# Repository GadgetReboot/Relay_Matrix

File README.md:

# Relay_Matrix
Relay matrix for routing signal inputs to various outputs

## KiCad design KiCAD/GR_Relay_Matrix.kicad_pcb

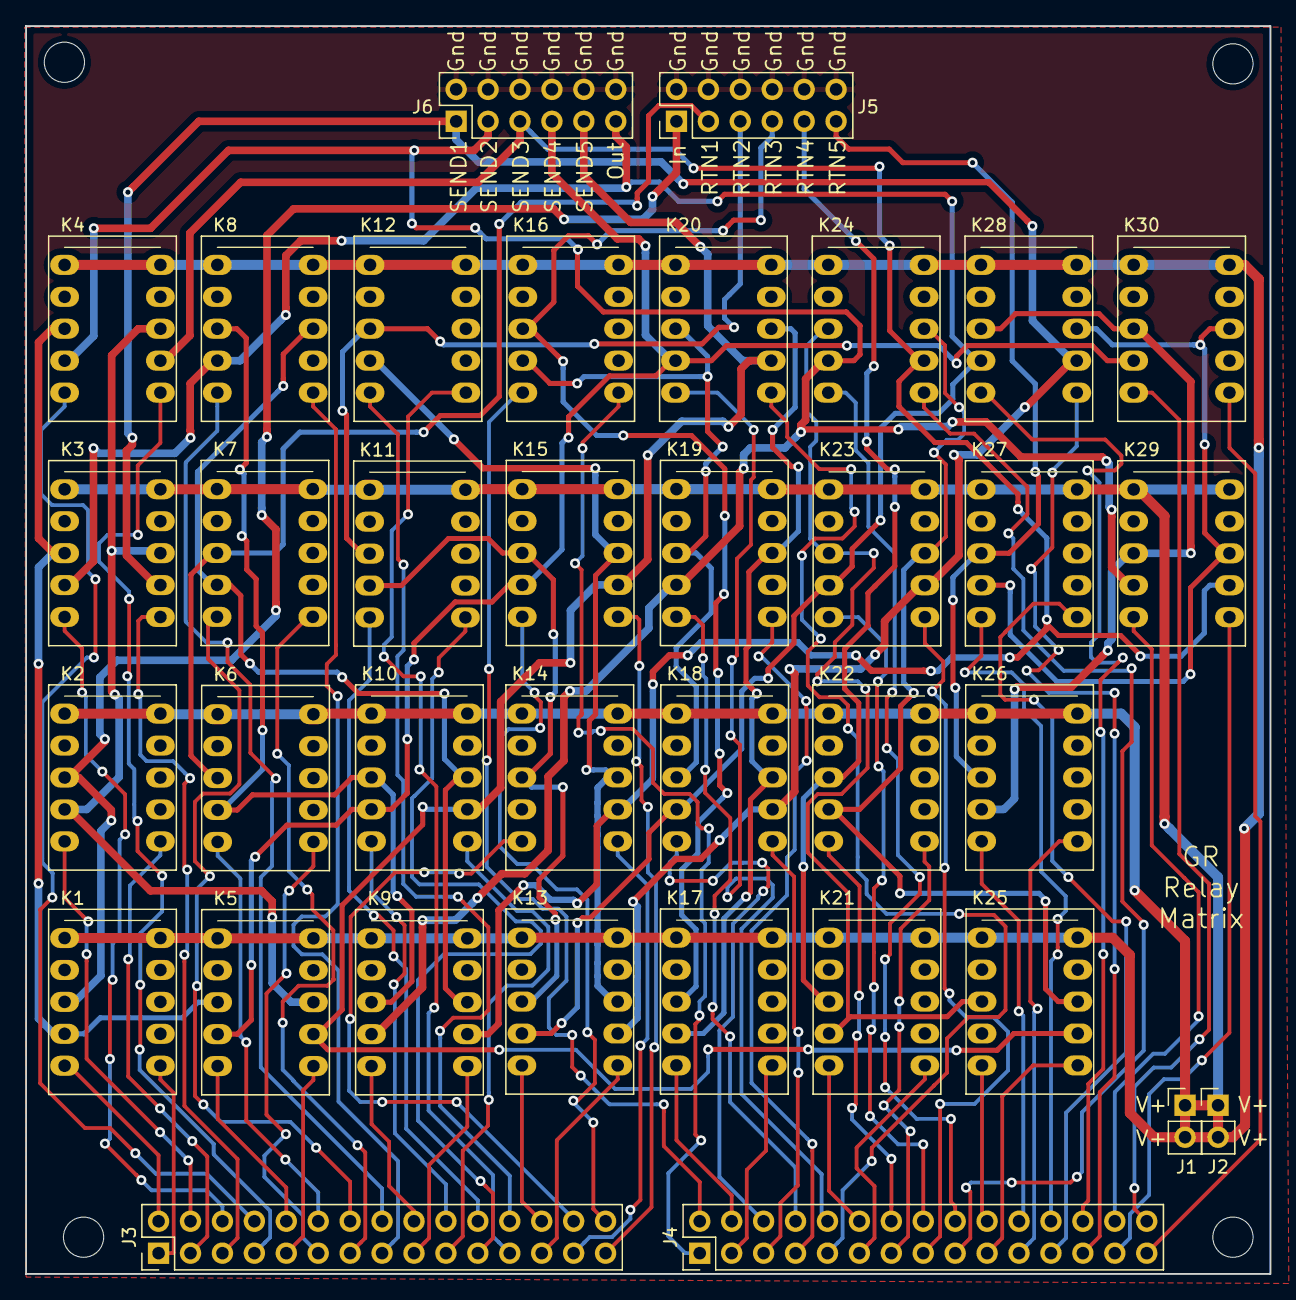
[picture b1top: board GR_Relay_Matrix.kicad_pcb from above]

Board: 2 copper layers, 99.0 x 99.3 mm, 40 parts (0 on the bottom side), 86 nets.

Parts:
J1, J2: Conn_01x02; PinHeader_1x02_P2.54mm_Vertical
J3, J4: Conn_02x15_Odd_Even; PinHeader_2x15_P2.54mm_Vertical
J5, J6: Conn_02x06_Odd_Even; PinHeader_2x06_P2.54mm_Vertical
K1, K2, K3, K4, K5, K6, K7, K8, K9, K10, K11, K12, K13, K14, K15, K16, K17, K18, K19, K20, K21, K22, K23, K24, K25, K26, K27, K28, K29, K30: EA2-5TNJ; Relay_DPDT_FRT5
MH1, MH2, MH3, MH4: MountingHole; MountingHole_3.2mm_M3

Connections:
/Main_In: J5.1, K1.3, K2.3
/Main_Out: J6.11, K3.4, K8.4, K13.4, K18.4, K23.4, K28.4
/X1_Reset_A: J3.1, K1.6
/X1_Reset_B: J3.3, K2.6
/X1_Set_A: J3.2, K1.5
/X1_Set_B: J3.4, K2.5
/X2_Path: J5.3, K6.3, K7.3
/X2_Reset_A: J3.11, K6.6
/X2_Reset_B: J3.13, K7.6
/X2_Set_A: J3.12, K6.5
/X2_Set_B: J3.14, K7.5
/X3_Path: J5.5, K11.3, K12.3
/X3_Reset_A: J3.21, K11.6
/X3_Reset_B: J3.23, K12.6
/X3_Set_A: J3.22, K11.5
/X3_Set_B: J3.24, K12.5
/X4_Path: J5.7, K16.3, K17.3
/X4_Reset_A: J4.1, K16.6
/X4_Reset_B: J4.3, K17.6
/X4_Set_A: J4.2, K16.5
/X4_Set_B: J4.4, K17.5
/X5_Path: J5.9, K21.3, K22.3
/X5_Reset_A: J4.11, K21.6
/X5_Reset_B: J4.13, K22.6
/X5_Set_A: J4.12, K21.5
/X5_Set_B: J4.14, K22.5
/X6_Path: J5.11, K26.3, K27.3
/X6_Reset_A: J4.21, K26.6
/X6_Reset_B: J4.23, K27.6
/X6_Set_A: J4.22, K26.5
/X6_Set_B: J4.24, K27.5
/Y1_2_Reset: J3.5, K3.6
/Y1_2_Set: J3.6, K3.5
/Y2_Path: J6.1, K3.7, K13.7, K18.7, K23.7, K28.7
/Y3_4_Reset: J3.7, K4.6
/Y3_4_Set: J3.8, K4.5
/Y3_Path: J6.3, K4.4, K9.4, K19.4, K24.4, K29.4
/Y4_Path: J6.5, K4.7, K9.7, K14.7, K24.7, K29.7
/Y5_6_Reset: J3.9, K5.6
/Y5_6_Set: J3.10, K5.5
/Y5_Path: J6.7, K5.4, K10.4, K15.4, K20.4, K30.4
/Y6_Path: J6.9, K5.7, K10.7, K15.7, K20.7, K25.7
/Y7_8_Reset: J3.15, K8.6
/Y7_8_Set: J3.16, K8.5
/Y9_10_Reset: J3.17, K9.6
/Y9_10_Set: J3.18, K9.5
/Y11_12_Reset: J3.19, K10.6
/Y11_12_Set: J3.20, K10.5
/Y13_14_Reset: J3.25, K13.6
/Y13_14_Set: J3.26, K13.5
/Y15_16_Reset: J3.27, K14.6
/Y15_16_Set: J3.28, K14.5
/Y17_18_Reset: J3.29, K15.6
/Y17_18_Set: J3.30, K15.5
/Y19_20_Reset: J4.5, K18.6
/Y19_20_Set: J4.6, K18.5
/Y21_22_Reset: J4.7, K19.6
/Y21_22_Set: J4.8, K19.5
/Y23_24_Reset: J4.9, K20.6
/Y23_24_Set: J4.10, K20.5
/Y25_26_Reset: J4.15, K23.6
/Y25_26_Set: J4.16, K23.5
/Y27_28_Reset: J4.17, K24.6
/Y27_28_Set: J4.18, K24.5
/Y29_30_Reset: J4.19, K25.6
/Y29_30_Set: J4.20, K25.5
/Y31_32_Reset: J4.25, K28.6
/Y31_32_Set: J4.26, K28.5
/Y33_34_Reset: J4.27, K29.6
/Y33_34_Set: J4.28, K29.5
/Y35_36_Reset: J4.29, K30.6
/Y35_36_Set: J4.30, K30.5
GNDREF: J5.2, J5.4, J5.6, J5.8, J5.10, J5.12, J6.2, J6.4, J6.6, J6.8, J6.10, J6.12
unnamed: K1.4, K3.3, K4.3, K5.3
unnamed: K2.4, K3.8, K4.8, K5.8
unnamed: K6.4, K8.3, K9.3, K10.3
unnamed: K7.4, K8.8, K9.8, K10.8
unnamed: K11.4, K13.3, K14.3, K15.3
unnamed: K12.4, K13.8, K14.8, K15.8
unnamed: K16.4, K18.3, K19.3, K20.3
unnamed: K17.4, K18.8, K19.8, K20.8
unnamed: K21.4, K23.3, K24.3, K25.3
unnamed: K22.4, K23.8, K24.8, K25.8
unnamed: K26.4, K28.3, K29.3, K30.3
unnamed: K27.4, K28.8, K29.8, K30.8
Vdrive: J1.1, J1.2, J2.1, J2.2, K1.1, K1.10, K2.1, K2.10, K3.1, K3.10, K4.1, K4.10, K5.1, K5.10, K6.1, K6.10, K7.1, K7.10, K8.1, K8.10, K9.1, K9.10, K10.1, K10.10, K11.1, K11.10, K12.1, K12.10, K13.1, K13.10, K14.1, K14.10, K15.1, K15.10, K16.1, K16.10, K17.1, K17.10, K18.1, K18.10, K19.1, K19.10, K20.1, K20.10, K21.1, K21.10, K22.1, K22.10, K23.1, K23.10, K24.1, K24.10, K25.1, K25.10, K26.1, K26.10, K27.1, K27.10, K28.1, K28.10, K29.1, K29.10, K30.1, K30.10

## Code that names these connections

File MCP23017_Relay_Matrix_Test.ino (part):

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
// Relay Matrix pcb driver signals to MCP23017 GPIO mapping
// x1 input to y output relays
#define x1_reset_A    10  // GPB2    starting at mcp23017 addr 0x20
#define x1_set_A      11  // GPB3
#define x1_reset_B    12  // GPB4
#define x1_set_B      13  // GPB5
#define y1_2_reset    14  // GPB6
#define y1_2_set      15  // GPB7
#define y3_4_reset    0   // GPA0
#define y3_4_set      1   // GPA1
#define y5_6_reset    2   // GPA2
#define y5_6_set      3   // GPA3

// x2 input to y output relays
#define x2_reset_A    4   // GPA4
#define x2_set_A      5   // GPA5
#define x2_reset_B    6   // GPA6
#define x2_set_B      7   // GPA7
#define y7_8_reset    8   // GPB0    starting at mcp23017 addr 0x21
#define y7_8_set      9   // GPB1
#define y9_10_reset   10  // GPB2
#define y9_10_set     11  // GPB3
#define y11_12_reset  12  // GPB4
#define y11_12_set    13  // GPB5

// x3 input to y output relays
#define x3_reset_A    14  // GPB6
#define x3_set_A      15  // GPB7
#define x3_reset_B    0   // GPA0
#define x3_set_B      1   // GPA1
#define y13_14_reset  2   // GPA2    
#define y13_14_set    3   // GPA3
#define y15_16_reset  4   // GPA4
#define y15_16_set    5   // GPA5
#define y17_18_reset  6   // GPA6
#define y17_18_set    7   // GPA7

// x4 input to y output relays
#define x4_reset_A    8   // GPB0    starting at mcp23017 addr 0x22
#define x4_set_A      9   // GPB1
#define x4_reset_B    10  // GPB2
#define x4_set_B      11  // GPB3
#define y19_20_reset  12  // GPB4    
#define y19_20_set    13  // GPB5
#define y21_22_reset  14  // GPB6
#define y21_22_set    15  // GPB7
#define y23_24_reset  0   // GPA0
#define y23_24_set    1   // GPA1

// x5 input to y output relays
#define x5_reset_A    2   // GPA2    
#define x5_set_A      3   // GPA3
#define x5_reset_B    4   // GPA4
#define x5_set_B      5   // GPA5
#define y25_26_reset  6   // GPA6    
#define y25_26_set    7   // GPA7
#define y27_28_reset  8   // GPB0    starting at mcp23017 addr 0x23
#define y27_28_set    9   // GPB1
#define y29_30_reset  10  // GPB2
#define y29_30_set    11  // GPB3

// x6 input to y output relays
#define x6_reset_A    12  // GPB4    
#define x6_set_A      13  // GPB5
#define x6_reset_B    14  // GPB6
#define x6_set_B      15  // GPB7
#define y31_32_reset  0   // GPA0    
#define y31_32_set    1   // GPA1
#define y33_34_reset  2   // GPA2     
#define y33_34_set    3   // GPA3
#define y35_36_reset  4   // GPA4
#define y35_36_set    5   // GPA5


// macros to turn relay channels on/off
#define x1_reset_A_on      mcp1.digitalWrite(x1_reset_A, 1)
#define x1_reset_A_off     mcp1.digitalWrite(x1_reset_A, 0)

#define x1_set_A_on        mcp1.digitalWrite(x1_set_A, 1)
#define x1_set_A_off       mcp1.digitalWrite(x1_set_A, 0)

#define x1_reset_B_on      mcp1.digitalWrite(x1_reset_B, 1)
#define x1_reset_B_off     mcp1.digitalWrite(x1_reset_B, 0)

#define x1_set_B_on        mcp1.digitalWrite(x1_set_B, 1)
#define x1_set_B_off       mcp1.digitalWrite(x1_set_B, 0)

#define y1_2_reset_on      mcp1.digitalWrite(y1_2_reset, 1)
#define y1_2_reset_off     mcp1.digitalWrite(y1_2_reset, 0)

#define y1_2_set_on        mcp1.digitalWrite(y1_2_set, 1)
#define y1_2_set_off       mcp1.digitalWrite(y1_2_set, 0)

#define y3_4_reset_on      mcp1.digitalWrite(y3_4_reset, 1)
#define y3_4_reset_off     mcp1.digitalWrite(y3_4_reset, 0)

#define y3_4_set_on        mcp1.digitalWrite(y3_4_set, 1)
#define y3_4_set_off       mcp1.digitalWrite(y3_4_set, 0)

#define y5_6_reset_on      mcp1.digitalWrite(y5_6_reset, 1)
#define y5_6_reset_off     mcp1.digitalWrite(y5_6_reset, 0)

#define y5_6_set_on        mcp1.digitalWrite(y5_6_set, 1)
#define y5_6_set_off       mcp1.digitalWrite(y5_6_set, 0)

#define x2_reset_A_on      mcp1.digitalWrite(x2_reset_A, 1)
#define x2_reset_A_off     mcp1.digitalWrite(x2_reset_A, 0)

#define x2_set_A_on        mcp1.digitalWrite(x2_set_A, 1)
#define x2_set_A_off       mcp1.digitalWrite(x2_set_A, 0)

#define x2_reset_B_on      mcp1.digitalWrite(x2_reset_B, 1)
#define x2_reset_B_off     mcp1.digitalWrite(x2_reset_B, 0)

#define x2_set_B_on        mcp1.digitalWrite(x2_set_B, 1)
#define x2_set_B_off       mcp1.digitalWrite(x2_set_B, 0)

#define y7_8_reset_on      mcp2.digitalWrite(y7_8_reset, 1)
#define y7_8_reset_off     mcp2.digitalWrite(y7_8_reset, 0)

#define y7_8_set_on        mcp2.digitalWrite(y7_8_set, 1)
#define y7_8_set_off       mcp2.digitalWrite(y7_8_set, 0)

#define y9_10_reset_on     mcp2.digitalWrite(y9_10_reset, 1)
#define y9_10_reset_off    mcp2.digitalWrite(y9_10_reset, 0)

#define y9_10_set_on       mcp2.digitalWrite(y9_10_set, 1)
#define y9_10_set_off      mcp2.digitalWrite(y9_10_set, 0)

#define y11_12_reset_on    mcp2.digitalWrite(y11_12_reset, 1)
#define y11_12_reset_off   mcp2.digitalWrite(y11_12_reset, 0)

#define y11_12_set_on      mcp2.digitalWrite(y11_12_set, 1)
#define y11_12_set_off     mcp2.digitalWrite(y11_12_set, 0)

#define x3_reset_A_on      mcp2.digitalWrite(x3_reset_A, 1)
#define x3_reset_A_off     mcp2.digitalWrite(x3_reset_A, 0)

#define x3_set_A_on        mcp2.digitalWrite(x3_set_A, 1)
#define x3_set_A_off       mcp2.digitalWrite(x3_set_A, 0)

#define x3_reset_B_on      mcp2.digitalWrite(x3_reset_B, 1)
#define x3_reset_B_off     mcp2.digitalWrite(x3_reset_B, 0)

#define x3_set_B_on        mcp2.digitalWrite(x3_set_B, 1)
#define x3_set_B_off       mcp2.digitalWrite(x3_set_B, 0)

#define y13_14_reset_on    mcp2.digitalWrite(y13_14_reset, 1)
#define y13_14_reset_off   mcp2.digitalWrite(y13_14_reset, 0)

#define y13_14_set_on      mcp2.digitalWrite(y13_14_set, 1)
#define y13_14_set_off     mcp2.digitalWrite(y13_14_set, 0)

#define y15_16_reset_on    mcp2.digitalWrite(y15_16_reset, 1)
#define y15_16_reset_off   mcp2.digitalWrite(y15_16_reset, 0)

#define y15_16_set_on      mcp2.digitalWrite(y15_16_set, 1)
#define y15_16_set_off     mcp2.digitalWrite(y15_16_set, 0)

#define y17_18_reset_on    mcp2.digitalWrite(y17_18_reset, 1)
#define y17_18_reset_off   mcp2.digitalWrite(y17_18_reset, 0)

#define y17_18_set_on      mcp2.digitalWrite(y17_18_set, 1)
#define y17_18_set_off     mcp2.digitalWrite(y17_18_set, 0)

#define x4_reset_A_on      mcp3.digitalWrite(x4_reset_A, 1)
#define x4_reset_A_off     mcp3.digitalWrite(x4_reset_A, 0)

#define x4_set_A_on        mcp3.digitalWrite(x4_set_A, 1)
#define x4_set_A_off       mcp3.digitalWrite(x4_set_A, 0)

#define x4_reset_B_on      mcp3.digitalWrite(x4_reset_B, 1)
#define x4_reset_B_off     mcp3.digitalWrite(x4_reset_B, 0)

#define x4_set_B_on        mcp3.digitalWrite(x4_set_B, 1)
#define x4_set_B_off       mcp3.digitalWrite(x4_set_B, 0)

#define y19_20_reset_on    mcp3.digitalWrite(y19_20_reset, 1)
#define y19_20_reset_off   mcp3.digitalWrite(y19_20_reset, 0)

#define y19_20_set_on      mcp3.digitalWrite(y19_20_set, 1)
#define y19_20_set_off     mcp3.digitalWrite(y19_20_set, 0)

#define y21_22_reset_on    mcp3.digitalWrite(y21_22_reset, 1)
#define y21_22_reset_off   mcp3.digitalWrite(y21_22_reset, 0)

#define y21_22_set_on      mcp3.digitalWrite(y21_22_set, 1)
#define y21_22_set_off     mcp3.digitalWrite(y21_22_set, 0)

#define y23_24_reset_on    mcp3.digitalWrite(y23_24_reset, 1)
#define y23_24_reset_off   mcp3.digitalWrite(y23_24_reset, 0)

#define y23_24_set_on      mcp3.digitalWrite(y23_24_set, 1)
#define y23_24_set_off     mcp3.digitalWrite(y23_24_set, 0)

#define x5_reset_A_on      mcp3.digitalWrite(x5_reset_A, 1)
#define x5_reset_A_off     mcp3.digitalWrite(x5_reset_A, 0)

#define x5_set_A_on        mcp3.digitalWrite(x5_set_A, 1)
#define x5_set_A_off       mcp3.digitalWrite(x5_set_A, 0)

#define x5_reset_B_on      mcp3.digitalWrite(x5_reset_B, 1)
#define x5_reset_B_off     mcp3.digitalWrite(x5_reset_B, 0)

#define x5_set_B_on        mcp3.digitalWrite(x5_set_B, 1)
#define x5_set_B_off       mcp3.digitalWrite(x5_set_B, 0)

#define y25_26_reset_on    mcp3.digitalWrite(y25_26_reset, 1)
#define y25_26_reset_off   mcp3.digitalWrite(y25_26_reset, 0)

#define y25_26_set_on      mcp3.digitalWrite(y25_26_set, 1)
#define y25_26_set_off     mcp3.digitalWrite(y25_26_set, 0)

#define y27_28_reset_on    mcp4.digitalWrite(y27_28_reset, 1)
#define y27_28_reset_off   mcp4.digitalWrite(y27_28_reset, 0)

#define y27_28_set_on      mcp4.digitalWrite(y27_28_set, 1)
#define y27_28_set_off     mcp4.digitalWrite(y27_28_set, 0)

#define y29_30_reset_on    mcp4.digitalWrite(y29_30_reset, 1)
#define y29_30_reset_off   mcp4.digitalWrite(y29_30_reset, 0)

#define y29_30_set_on      mcp4.digitalWrite(y29_30_set, 1)
#define y29_30_set_off     mcp4.digitalWrite(y29_30_set, 0)

#define x6_reset_A_on      mcp4.digitalWrite(x6_reset_A, 1)
#define x6_reset_A_off     mcp4.digitalWrite(x6_reset_A, 0)

#define x6_set_A_on        mcp4.digitalWrite(x6_set_A, 1)
#define x6_set_A_off       mcp4.digitalWrite(x6_set_A, 0)

#define x6_reset_B_on      mcp4.digitalWrite(x6_reset_B, 1)
#define x6_reset_B_off     mcp4.digitalWrite(x6_reset_B, 0)

#define x6_set_B_on        mcp4.digitalWrite(x6_set_B, 1)
#define x6_set_B_off       mcp4.digitalWrite(x6_set_B, 0)
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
